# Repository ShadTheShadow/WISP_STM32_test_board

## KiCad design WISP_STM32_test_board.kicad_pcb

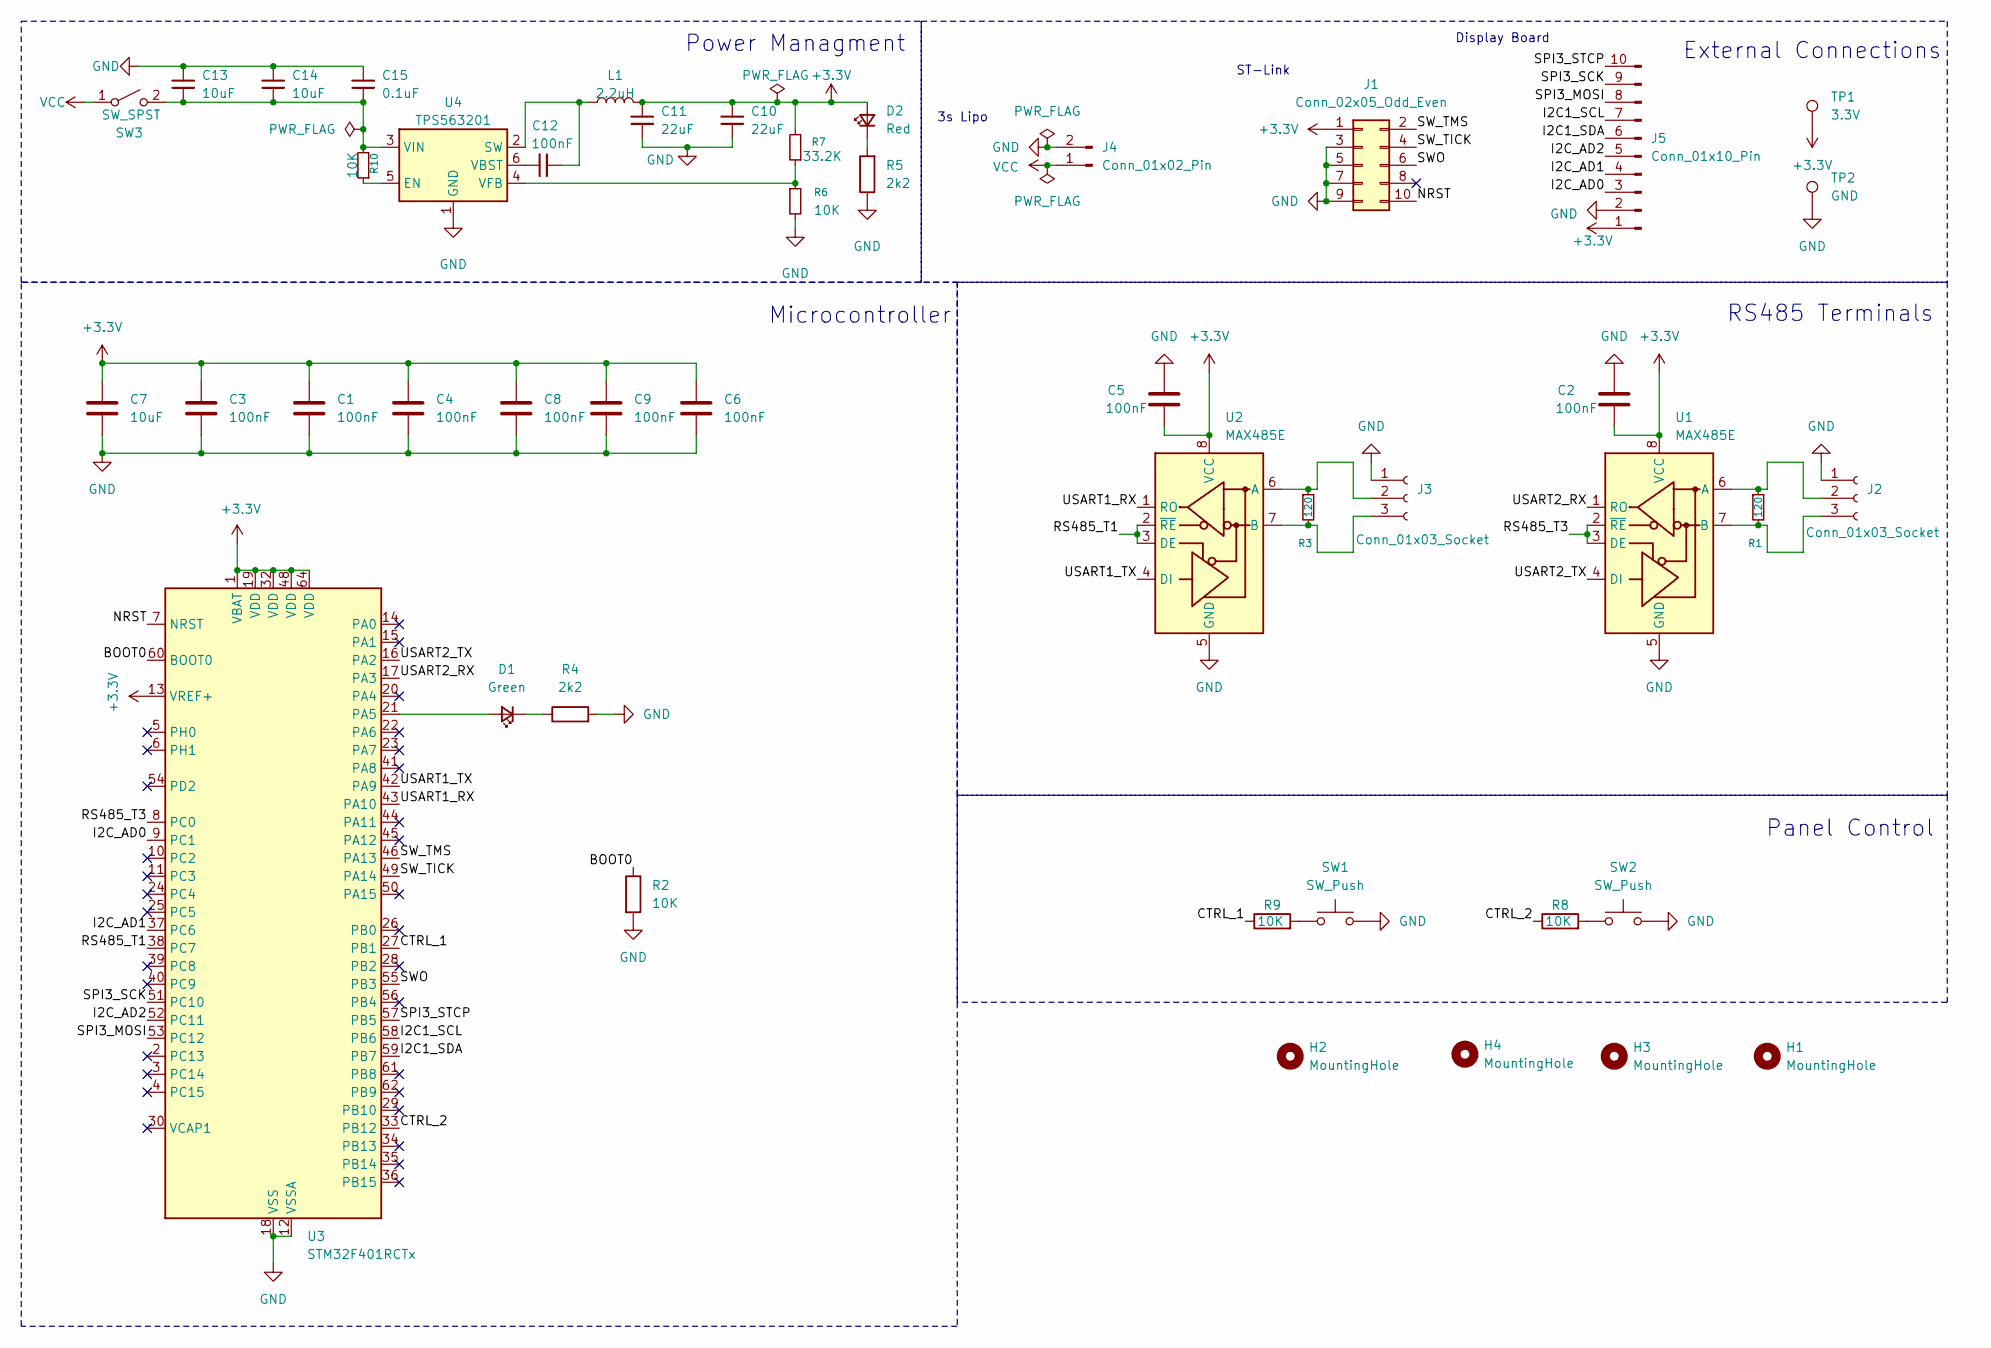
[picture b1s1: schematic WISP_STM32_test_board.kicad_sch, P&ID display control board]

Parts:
C1, C2, C3, C4, C5, C6, C8, C9, C12: 100nF; C_0603_1608Metric; Digikey Part # C0603C104K5RACTU
C7, C13: 10uF; C_0603_1608Metric; Digikey Part # EMK107BBJ106MA-T
C10, C11: 22uF; C_1206_3216Metric; Digikey Part # EMK316BB7226ML-T
C14: 10uF; C_1206_3216Metric; Digikey Part # C1206C106K4RACTU
C15: 0.1uF; C_1206_3216Metric; Digikey Part # C1206C104K5RACTU
D1: Green; LED_0603_1608Metric; Digikey Part # LTST-C190GKT
D2: Red; LED_0603_1608Metric; Digikey Part # LTST-C190KRKT
H1, H2, H3, H4: MountingHole; MountingHole_2.2mm_M2
J1: Conn_02x05_Odd_Even; PinHeader_2x05_P2.54mm_Vertical; Digikey Part # 732-2672-ND
J2, J3: Conn_01x03_Socket; TerminalBlock_Xinya_XY308-2.54-3P_1x03_P2.54mm_Horizontal; Digikey Part # ED10562-ND
J4: Conn_01x02_Pin; PinSocket_1x02_P2.54mm_Vertical
J5: Conn_01x10_Pin; PinHeader_1x10_P2.54mm_Vertical
L1: 2.2uH; L_Taiyo-Yuden_MD-4040; Digikey Part # NRS4018T2R2MDGJ
R1, R3: 120; R_0603_1608Metric; Digikey Part # ERA-3AEB121V
R2, R6, R8, R9, R10: 10K; R_0603_1608Metric; Digikey Part # CRCW060310K0FKEA
R4, R5: 2k2; R_0603_1608Metric; Digikey Part # RC0603JR-072K2L
R7: 33.2K; R_0603_1608Metric; Digikey Part # CRCW060333K2FKEAC
SW1, SW2: SW_Push; SW_PUSH_6mm; Digikey Part # 450-1650-ND
SW3: SW_SPST; SW_CK_JS202011CQN_DPDT_Straight; Digikey Part # 401-2001-ND
TP1: 3.3V; CUSTOM_TestPoint_Pad_1.0x1.0mm
TP2: GND; CUSTOM_TestPoint_Pad_1.0x1.0mm
U1, U2: MAX485E; SOIC-8_3.9x4.9mm_P1.27mm; Digikey Part # MAX3483CSA+T
U3: STM32F401RCTx; LQFP-64_10x10mm_P0.5mm; Mouser Part # 511-STM32F401RCT6
U4: TPS563201; SOT-23-6; Digikey Part # TPS563201DDCR

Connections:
+3.3V: C1.1, C2.2, C3.1, C4.1, C5.2, C6.1, C7.1, C8.1, C9.1, C10.1, C11.1, D2.2 (A), J1.1, J5.1, L1.2, R7.2, TP1.1 (1_1), U1.8 (VCC), U2.8 (VCC), U3.1 (VBAT), U3.13 (VREF+), U3.19 (VDD), U3.32 (VDD), U3.48 (VDD), U3.64 (VDD)
/BOOT0: R2.1, U3.60 (BOOT0)
/CTRL_1: R9.1, U3.27 (PB1)
/CTRL_2: R8.1, U3.33 (PB12)
/I2C1_SCL: J5.7, U3.58 (PB6)
/I2C1_SDA: J5.6, U3.59 (PB7)
/I2C_AD0: J5.3, U3.9 (PC1)
/I2C_AD1: J5.4, U3.37 (PC6)
/I2C_AD2: J5.5, U3.52 (PC11)
/NRST: J1.10, U3.7 (NRST)
/RS485_T1: U2.2 (~RE), U2.3 (DE), U3.38 (PC7)
/RS485_T3: U1.2 (~RE), U1.3 (DE), U3.8 (PC0)
/SPI3_MOSI: J5.8, U3.53 (PC12)
/SPI3_SCK: J5.9, U3.51 (PC10)
/SPI3_STCP: J5.10, U3.57 (PB5)
/SWO: J1.6, U3.55 (PB3)
/SW_TICK: J1.4, U3.49 (PA14)
/SW_TMS: J1.2, U3.46 (PA13)
/USART1_RX: U2.1 (RO), U3.43 (PA10)
/USART1_TX: U2.4 (DI), U3.42 (PA9)
/USART2_RX: U1.1 (RO), U3.17 (PA3)
/USART2_TX: U1.4 (DI), U3.16 (PA2)
GND: C1.2, C2.1, C3.2, C4.2, C5.1, C6.2, C7.2, C8.2, C9.2, C10.2, C11.2, C13.1, C14.1, C15.1, J1.3, J1.5, J1.7, J1.9, J2.1, J3.1, J4.2, J5.2, R2.2, R4.2, R5.1, R6.2, SW1.2, SW2.2, TP2.1 (1_1), U1.5 (GND), U2.5 (GND), U3.12 (VSSA), U3.18 (VSS), U3.31 (VSS), U3.47 (VSS), U3.63 (VSS), U4.1 (GND)
unnamed: D1.2 (A), U3.21 (PA5)
unnamed: D1.1 (K), R4.1
unnamed: D2.1 (K), R5.2
unnamed: J2.2, R1.1, U1.6 (A)
unnamed: J2.3, R1.2, U1.7 (B)
unnamed: J3.2, R3.1, U2.6 (A)
unnamed: J3.3, R3.2, U2.7 (B)
unnamed: R8.2, SW2.1
unnamed: R9.2, SW1.1
unnamed: C13.2, C14.2, C15.2, R10.2, SW3.2 (B), U4.3 (VIN)
unnamed: R10.1, U4.5 (EN)
unnamed: C12.2, L1.1, U4.2 (SW)
unnamed: C12.1, U4.6 (VBST)
unnamed: R6.1, R7.1, U4.4 (VFB)
VCC: J4.1, SW3.1 (A)

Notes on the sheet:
Panel Control
3s Lipo
RS485 Terminals
Display Board
Microcontroller
Power Managment
ST-Link
External Connections

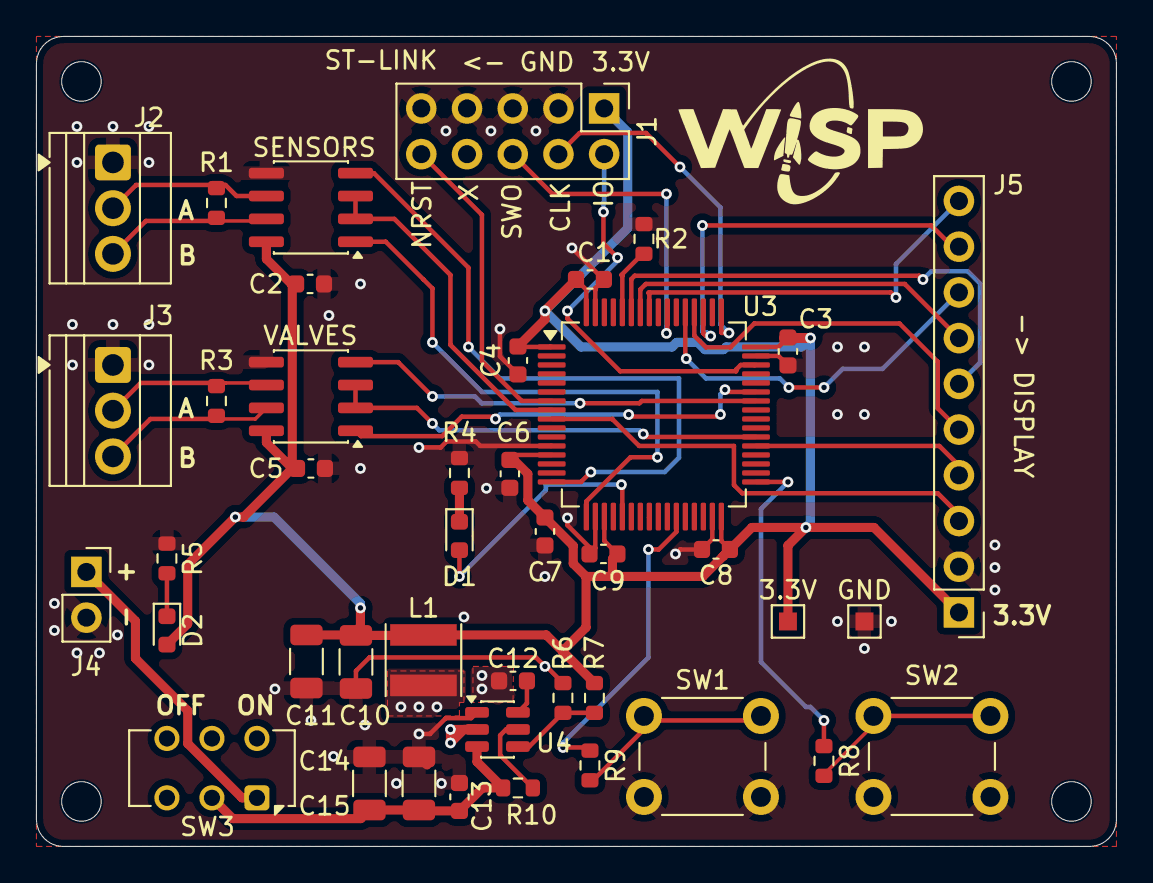
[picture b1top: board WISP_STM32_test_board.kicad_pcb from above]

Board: 2 copper layers, 60.0 x 45.0 mm, 46 parts (0 on the bottom side), 38 nets.

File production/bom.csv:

Designator,Footprint,Quantity,Value,LCSC Part #
"C1, C3, C4, C6, C8, C9",0603,6,100nF,
"C10, C11",1206,2,22uF,
"C12, C2, C5",0603,3,0.1uF,
"C13, C7",0603,2,10uF,
C14,1206,1,10uF,
C15,1206,1,0.1uF,
D1,0603,1,Green,
D2,0603,1,Red,
J1,PinHeader_2x05_P2.54mm_Vertical,1,Conn_02x05_Odd_Even,
"J2, J3",TerminalBlock_Xinya_XY308-2.54-3P_1x03_P2.54mm_Horizontal,2,Conn_01x03_Socket,
J4,PinSocket_1x02_P2.54mm_Vertical,1,Conn_01x02_Pin,
J5,PinHeader_1x10_P2.54mm_Vertical,1,Conn_01x10_Pin,
L1,L_Taiyo-Yuden_MD-4040,1,2.2uH,
"R1, R3",0603,2,120,
"R10, R2, R6, R8, R9",0603,5,10K,
"R4, R5",0603,2,2k2,
R7,0603,1,33.2K,
"SW1, SW2",SW_PUSH_6mm,2,SW_Push,
SW3,SW_CK_JS202011CQN_DPDT_Straight,1,SW_SPST,
TP1,CUSTOM_TestPoint_Pad_1.0x1.0mm,1,3.3V,
TP2,CUSTOM_TestPoint_Pad_1.0x1.0mm,1,GND,
"U1, U2",SOIC-8_3.9x4.9mm_P1.27mm,2,MAX485E,
U3,LQFP-64_10x10mm_P0.5mm,1,STM32F401RCTx,
U4,SOT-23-6,1,TPS563201,
